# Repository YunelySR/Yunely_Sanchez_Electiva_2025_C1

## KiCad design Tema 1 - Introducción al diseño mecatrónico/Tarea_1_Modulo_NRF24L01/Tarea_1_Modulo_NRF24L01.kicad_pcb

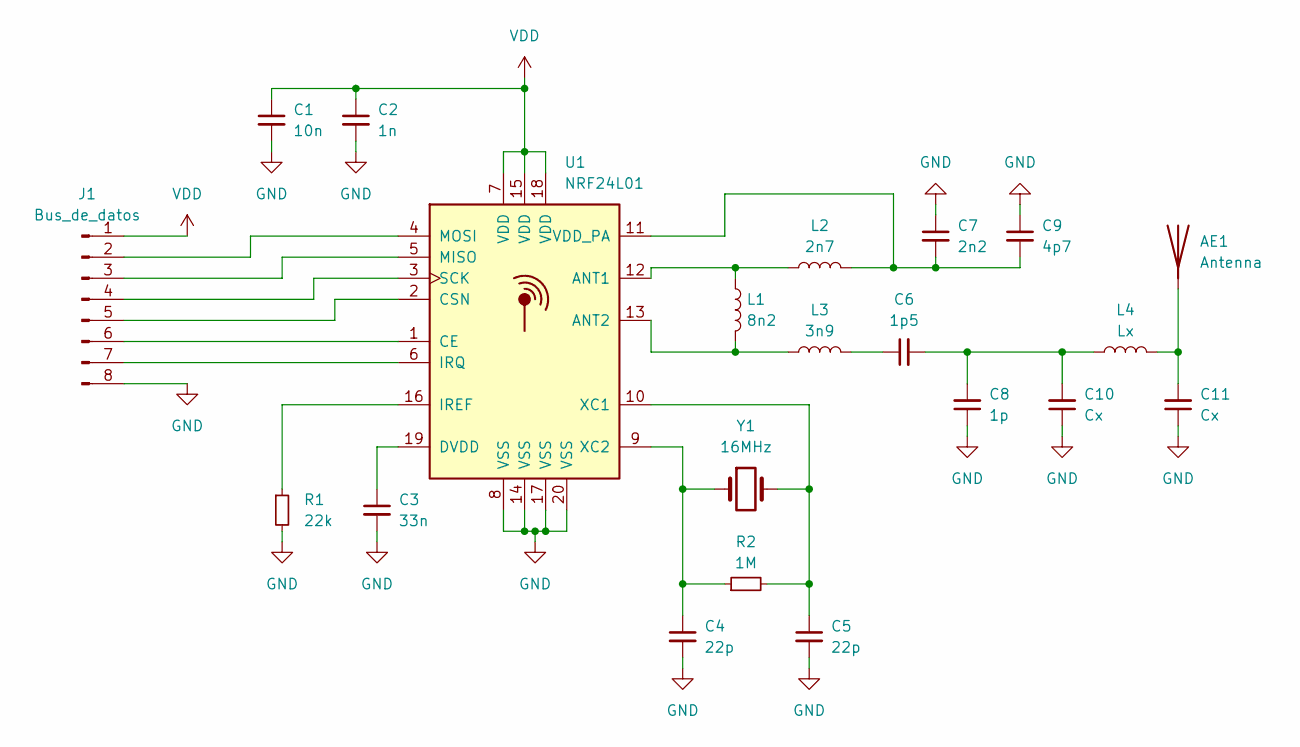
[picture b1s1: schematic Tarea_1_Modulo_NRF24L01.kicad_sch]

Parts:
AE1: Antenna; Texas_SWRA117D_2.4GHz_Right
C1: 10n; C_0402_1005Metric
C2: 1n; C_0402_1005Metric
C3: 33n; C_0402_1005Metric
C4, C5: 22p; C_0402_1005Metric
C6: 1p5; C_0402_1005Metric
C7: 2n2; C_0402_1005Metric
C8: 1p; C_0402_1005Metric
C9: 4p7; C_0402_1005Metric
C10, C11: Cx; C_0402_1005Metric
J1: Bus_de_datos; Hirose_DF13-08P-1.25DSA_1x08_P1.25mm_Vertical
L1: 8n2; L_0402_1005Metric
L2: 2n7; L_0402_1005Metric
L3: 3n9; L_0402_1005Metric
L4: Lx; L_0402_1005Metric
R1: 22k; R_0402_1005Metric
R2: 1M; R_0402_1005Metric
U1: NRF24L01; QFN-20-1EP_4x4mm_P0.5mm_EP2.5x2.5mm
Y1: 16MHz; Crystal_SMD_3215-2Pin_3.2x1.5mm

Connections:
GND: C1.2, C2.2, C3.2, C4.2, C5.2, C7.1, C8.1, C9.1, C10.1, C11.1, J1.8, R1.2, U1.8 (VSS), U1.14 (VSS), U1.17 (VSS), U1.20 (VSS)
unnamed: AE1.1 (A), C11.2, L4.2
unnamed: C6.1, L3.2
unnamed: C6.2, C8.2, C10.2, L4.1
unnamed: J1.2, U1.4 (MOSI)
unnamed: J1.3, U1.5 (MISO)
unnamed: J1.4, U1.3 (SCK)
unnamed: J1.5, U1.2 (CSN)
unnamed: J1.6, U1.1 (CE)
unnamed: J1.7, U1.6 (IRQ)
unnamed: L1.1, L2.1, U1.12 (ANT1)
unnamed: L1.2, L3.1, U1.13 (ANT2)
unnamed: C3.1, U1.19 (DVDD)
unnamed: R1.1, U1.16 (IREF)
unnamed: C7.2, C9.2, L2.2, U1.11 (VDD_PA)
unnamed: C5.1, R2.2, U1.10 (XC1), Y1.2
unnamed: C4.1, R2.1, U1.9 (XC2), Y1.1
VDD: C1.1, C2.1, J1.1, U1.7 (VDD), U1.15 (VDD), U1.18 (VDD)

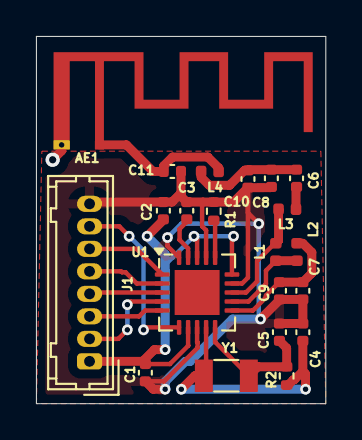
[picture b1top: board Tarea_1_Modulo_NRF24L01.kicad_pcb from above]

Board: 2 copper layers, 16.1 x 20.4 mm, 21 parts (0 on the bottom side), 18 nets.

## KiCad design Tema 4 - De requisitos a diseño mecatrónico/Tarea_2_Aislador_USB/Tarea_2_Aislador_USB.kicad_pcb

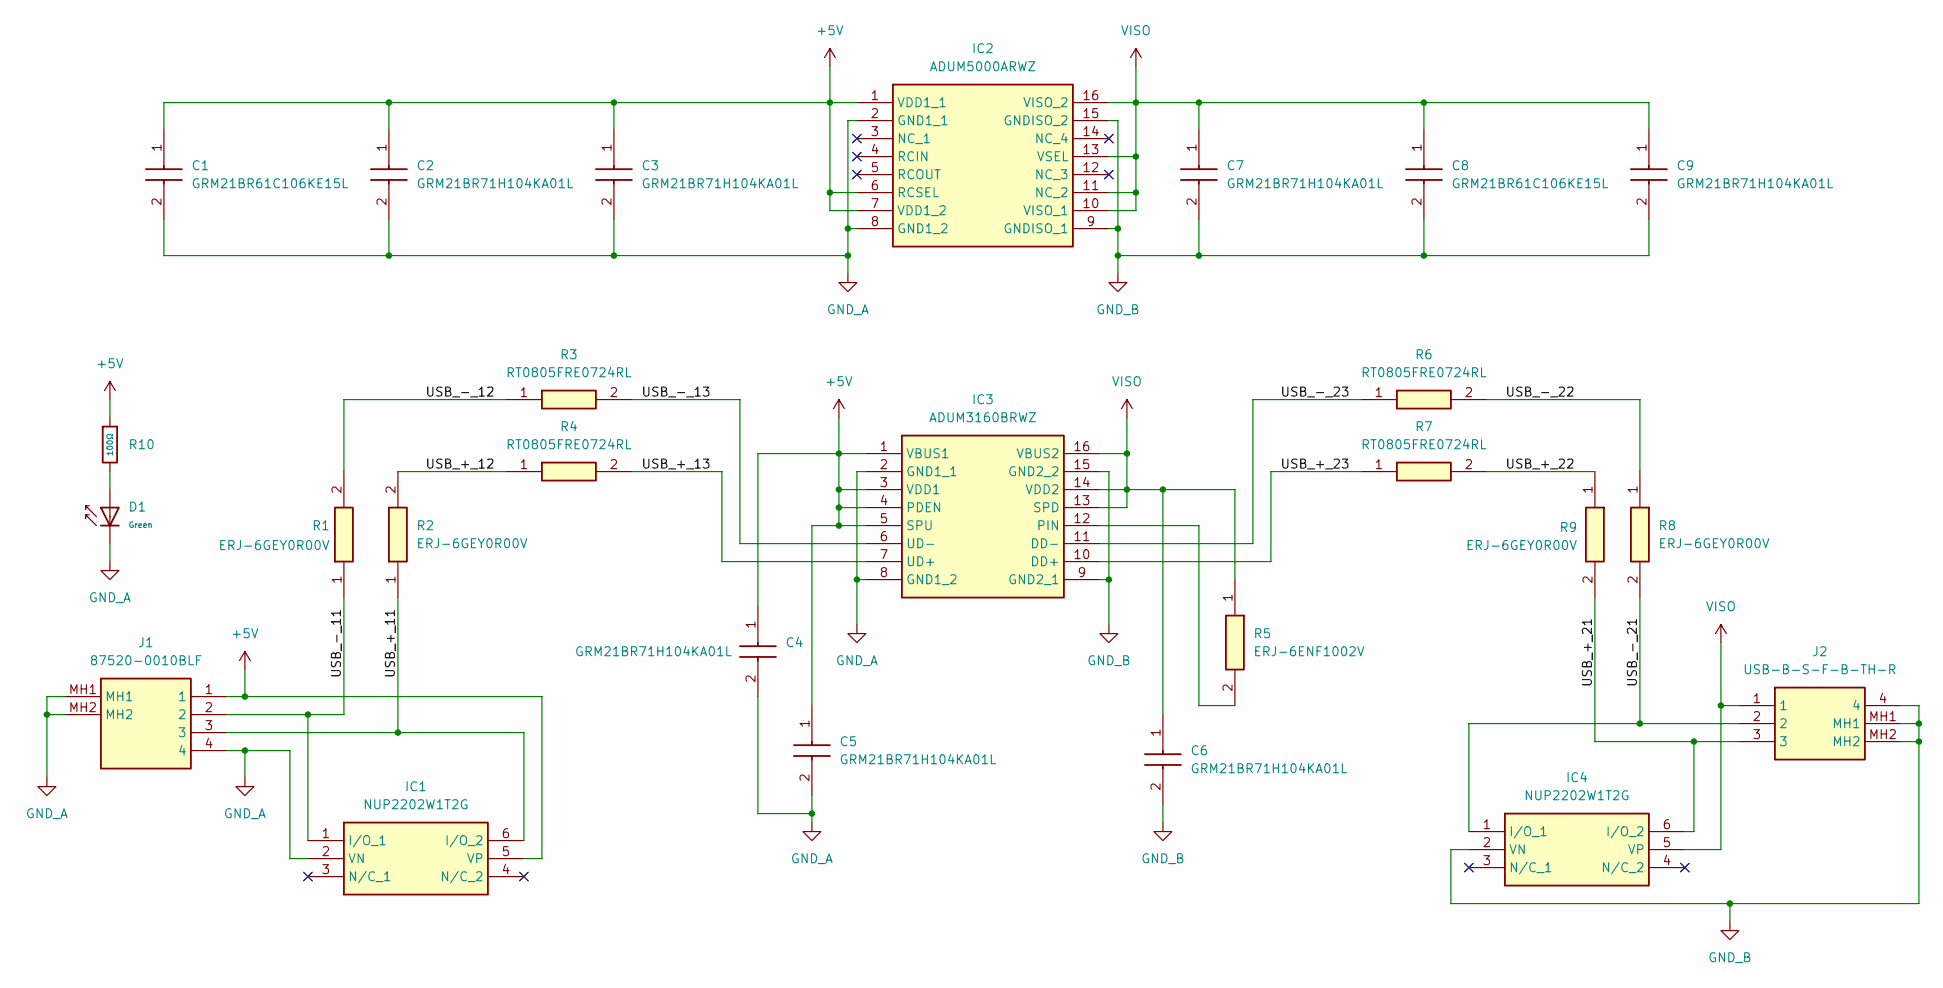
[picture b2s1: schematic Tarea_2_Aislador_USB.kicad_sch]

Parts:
C1, C8: GRM21BR61C106KE15L; CAPC2012X145N; Manufacturer_Part_Number GRM21BR61C106KE15L; Mouser Part Number 81-GRM21BR61C106KE15
C2, C3, C4, C5, C6, C7, C9: GRM21BR71H104KA01L; CAPC2012X145N; Manufacturer_Part_Number GRM21BR71H104KA01L; Mouser Part Number 81-GRM40X104K50L
D1: Green; D_0603; Part 19-217/GHC-YR1S2/6T; LCSC C2986059
IC1, IC4: NUP2202W1T2G; SOT65P210X110-6N; Manufacturer_Part_Number NUP2202W1T2G; Mouser Part Number 863-NUP2202W1T2G
IC2: ADUM5000ARWZ; SOIC127P1032X265-16N; Manufacturer_Part_Number ADUM5000ARWZ; Mouser Part Number 584-ADUM5000ARWZ
IC3: ADUM3160BRWZ; SOIC127P1032X265-16N; Manufacturer_Part_Number ADUM3160BRWZ; Mouser Part Number 584-ADUM3160BRWZ
J1: 87520-0010BLF; 875200010BLF; Manufacturer_Part_Number 87520-0010BLF
J2: USB-B-S-F-B-TH-R; USBBSFBTHR; Manufacturer_Part_Number USB-B-S-F-B-TH-R; Mouser Part Number 200-USBBSFBTHR
R1, R2, R8, R9: ERJ-6GEY0R00V; RESC2012X70N; Manufacturer_Part_Number ERJ-6GEY0R00V; Mouser Part Number 667-ERJ-6GEY0R00V
R3, R4, R6, R7: RT0805FRE0724RL; RESC2012X60N; Manufacturer_Part_Number RT0805FRE0724RL
R5: ERJ-6ENF1002V; ERJ6ENF1000V; Manufacturer_Part_Number ERJ-6ENF1002V; Mouser Part Number 667-ERJ-6ENF1002V
R10: 100Ω; R_0603; Overload Voltage (Max) 75V; Tolerance ±1%; Part 0603WAF1000T5E; LCSC C22775

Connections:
+5V: C1.1, C2.1, C3.1, C4.1, C5.1, IC1.5 (VP), IC2.1 (VDD1_1), IC2.6 (RCSEL), IC2.7 (VDD1_2), IC3.1 (VBUS1), IC3.3 (VDD1), IC3.4 (PDEN), IC3.5 (SPU), J1.1, R10.1
/USB_+_11: IC1.6 (I/O_2), J1.3, R2.1
/USB_+_12: R2.2, R4.1
/USB_+_13: IC3.7 (UD+), R4.2
/USB_+_21: IC4.6 (I/O_2), J2.3, R9.2
/USB_+_22: R7.2, R9.1
/USB_+_23: IC3.10 (DD+), R7.1
/USB_-_11: IC1.1 (I/O_1), J1.2, R1.1
/USB_-_12: R1.2, R3.1
/USB_-_13: IC3.6 (UD-), R3.2
/USB_-_21: IC4.1 (I/O_1), J2.2, R8.2
/USB_-_22: R6.2, R8.1
/USB_-_23: IC3.11 (DD-), R6.1
GND_A: C1.2, C2.2, C3.2, C4.2, C5.2, D1.1, IC1.2 (VN), IC2.2 (GND1_1), IC2.8 (GND1_2), IC3.2 (GND1_1), IC3.8 (GND1_2), J1.4, J1.MH1, J1.MH2
GND_B: C6.2, C7.2, C8.2, C9.2, IC2.9 (GNDISO_1), IC2.15 (GNDISO_2), IC3.9 (GND2_1), IC3.15 (GND2_2), IC4.2 (VN), J2.4, J2.MH1, J2.MH2
unnamed: D1.2, R10.2
unnamed: IC3.12 (PIN), R5.2
VISO: C6.1, C7.1, C8.1, C9.1, IC2.10 (VISO_1), IC2.11 (NC_2), IC2.13 (VSEL), IC2.16 (VISO_2), IC3.13 (SPD), IC3.14 (VDD2), IC3.16 (VBUS2), IC4.5 (VP), J2.1, R5.1

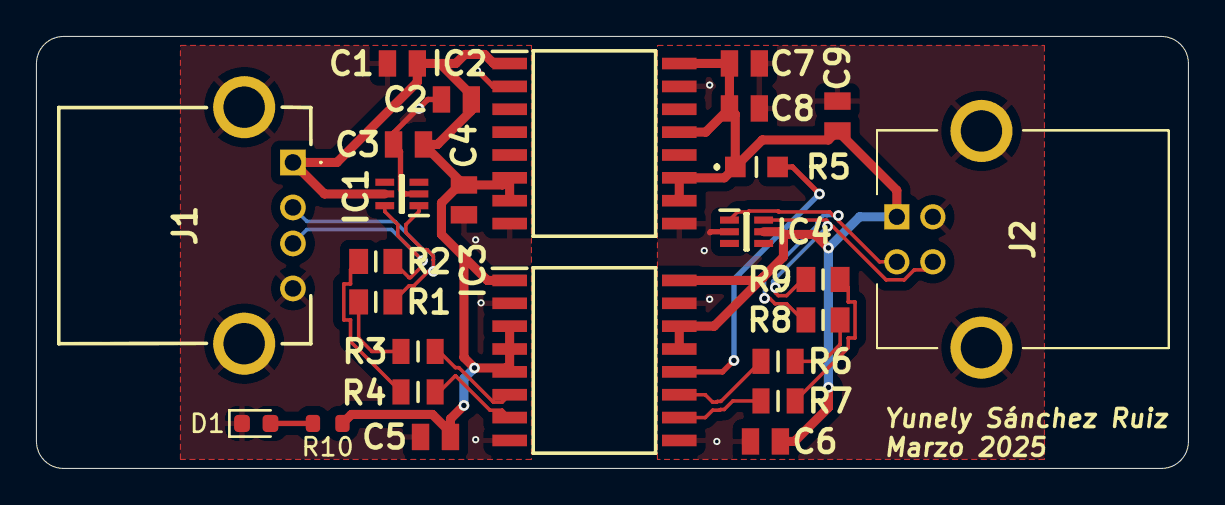
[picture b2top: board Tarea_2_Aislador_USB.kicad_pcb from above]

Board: 2 copper layers, 64.0 x 24.0 mm, 26 parts (0 on the bottom side), 18 nets.

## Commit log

2025-01-23 Esquemático listo
2025-01-23 PCB completado
2025-01-30 Resúmenes de los capítulos 1 y 2 del libro
2025-02-05 Notas clase 2 y 3 y selección de componentes
2025-02-05 modificación de la lista de componentes
2025-02-09 Apuntes clase 4
2025-02-13 Actualización de la librería de componentes: bobinas y transistores completos
2025-02-28 Clase 5 y 6 y actualización de la librería de componentes
2025-03-05 Esquemático de la tarea 2 listo
2025-03-05 PCB de la tarea 2 finalizado
2025-03-10 Actualización del aislador USB
2025-03-21 Librería de componentes y archivo de requisitos del proyecto
2025-04-21 Carcasa hecha en FreeCAD
2025-04-25 Diseño de la carcasa en Solid Edge
2025-04-25 Apuntes de la clase 10
